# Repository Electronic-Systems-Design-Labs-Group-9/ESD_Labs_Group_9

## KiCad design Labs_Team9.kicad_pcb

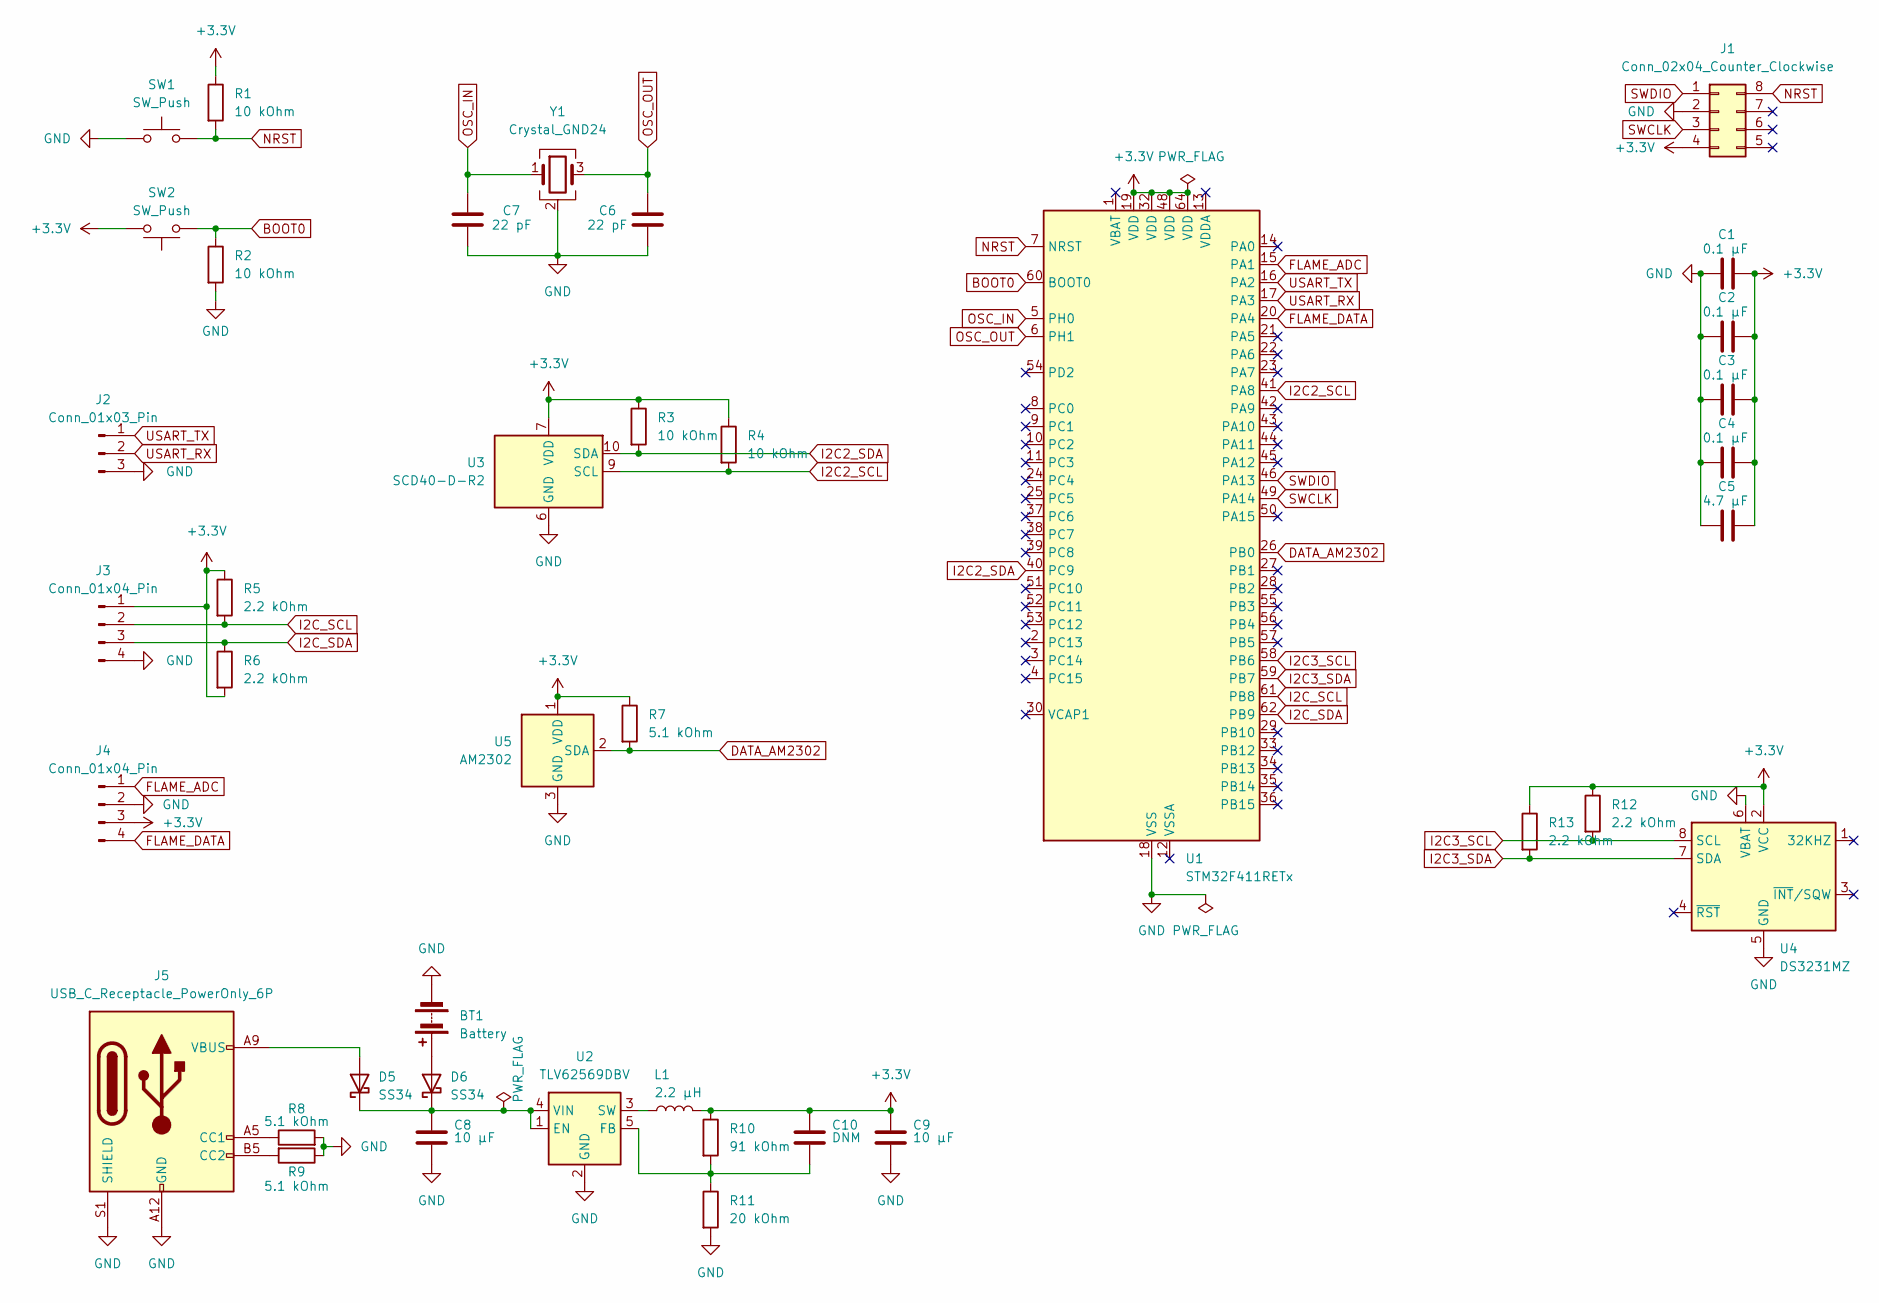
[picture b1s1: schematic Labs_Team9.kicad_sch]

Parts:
BT1: Battery; BatteryHolder_Keystone_2479_3xAAA
C1, C2, C3, C4: 0.1 μF; C_1206_3216Metric_Pad1.33x1.80mm_HandSolder
C5: 4.7 μF; C_1206_3216Metric_Pad1.33x1.80mm_HandSolder
C6, C7: 22 pF; C_1206_3216Metric_Pad1.33x1.80mm_HandSolder
C8, C9: 10 μF; C_1206_3216Metric_Pad1.33x1.80mm_HandSolder
C10: DNM; C_1206_3216Metric_Pad1.33x1.80mm_HandSolder
D5, D6: SS34; D_SMA_Handsoldering
J1: Conn_02x04_Counter_Clockwise; PinHeader_2x04_P2.54mm_Vertical
J2: Conn_01x03_Pin; PinHeader_1x03_P2.54mm_Vertical
J3, J4: Conn_01x04_Pin; PinHeader_1x04_P2.54mm_Vertical
J5: USB_C_Receptacle_PowerOnly_6P; USB_C_Receptacle_GCT_USB4135-GF-A_6P_TopMnt_Horizontal
L1: 2.2 μH; L_0805_2012Metric_Pad1.05x1.20mm_HandSolder
R1, R2, R3, R4: 10 kOhm; R_1206_3216Metric_Pad1.30x1.75mm_HandSolder
R5, R6, R12, R13: 2.2 kOhm; R_1206_3216Metric_Pad1.30x1.75mm_HandSolder
R7, R8, R9: 5.1 kOhm; R_1206_3216Metric_Pad1.30x1.75mm_HandSolder
R10: 91 kOhm; R_1206_3216Metric_Pad1.30x1.75mm_HandSolder
R11: 20 kOhm; R_1206_3216Metric_Pad1.30x1.75mm_HandSolder
SW1, SW2: SW_Push; SW_PUSH_6mm
U1: STM32F411RETx; LQFP-64_10x10mm_P0.5mm
U2: TLV62569DBV; SOT-23-5
U3: SCD40-D-R2; Sensirion_SCD4x-1EP_10.1x10.1mm_P1.25mm_EP4.8x4.8mm
U4: DS3231MZ; SOIC-8_3.9x4.9mm_P1.27mm
U5: AM2302; ASAIR_AM2302_P2.54mm_Lead2.75mm_TabDown
Y1: Crystal_GND24; Crystal_SMD_Abracon_ABM3C-4Pin_5.0x3.2mm

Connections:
+3.3V: C1.2, C2.2, C3.2, C4.2, C5.2, C9.1, C10.1, J1.4, J3.1, J4.3, L1.2, R1.1, R3.1, R4.1, R5.1, R6.2, R7.1, R10.1, R12.1, R13.1, SW2.2, U1.19 (VDD), U1.32 (VDD), U1.48 (VDD), U1.64 (VDD), U3.7 (VDD), U3.19 (VDD), U4.2 (VCC), U5.1 (VDD)
BOOT0: R2.1, SW2.1, U1.60 (BOOT0)
DATA_AM2302: R7.2, U1.26 (PB0), U5.2 (SDA)
FLAME_ADC: J4.1, U1.15 (PA1)
FLAME_DATA: J4.4, U1.20 (PA4)
GND: BT1.2 (-), C1.1, C2.1, C3.1, C4.1, C5.1, C6.1, C7.2, C8.2, C9.2, J1.2, J2.3, J3.4, J4.2, J5.A12 (GND), J5.B12 (GND), J5.S1 (SHIELD), R2.2, R8.2, R9.1, R11.2, SW1.1, U1.18 (VSS), U1.31 (VSS), U1.47 (VSS), U1.63 (VSS), U2.2 (GND), U3.6 (GND), U3.20 (GND), U3.21 (GND), U4.5 (GND), U4.6 (VBAT), U5.3 (GND), U5.4 (GND), Y1.2 (G), Y1.4 (G)
I2C2_SCL: R4.2, U1.41 (PA8), U3.9 (SCL)
I2C2_SDA: R3.2, U1.40 (PC9), U3.10 (SDA)
I2C3_SCL: R12.2, U1.58 (PB6), U4.8 (SCL)
I2C3_SDA: R13.2, U1.59 (PB7), U4.7 (SDA)
I2C_SCL: J3.2, R5.2, U1.61 (PB8)
I2C_SDA: J3.3, R6.1, U1.62 (PB9)
NRST: J1.8, R1.2, SW1.2, U1.7 (NRST)
unnamed: BT1.1 (+), D6.2 (A)
unnamed: D5.2 (A), J5.A9 (VBUS), J5.B9 (VBUS)
unnamed: C8.1, D5.1 (K), D6.1 (K), U2.1 (EN), U2.4 (VIN)
unnamed: J5.A5 (CC1), R8.1
unnamed: J5.B5 (CC2), R9.2
unnamed: C10.2, R10.2, R11.1, U2.5 (FB)
unnamed: L1.1, U2.3 (SW)
OSC_IN: C7.1, U1.5 (PH0), Y1.1
OSC_OUT: C6.2, U1.6 (PH1), Y1.3
SWCLK: J1.3, U1.49 (PA14)
SWDIO: J1.1, U1.46 (PA13)
USART_RX: J2.2, U1.17 (PA3)
USART_TX: J2.1, U1.16 (PA2)

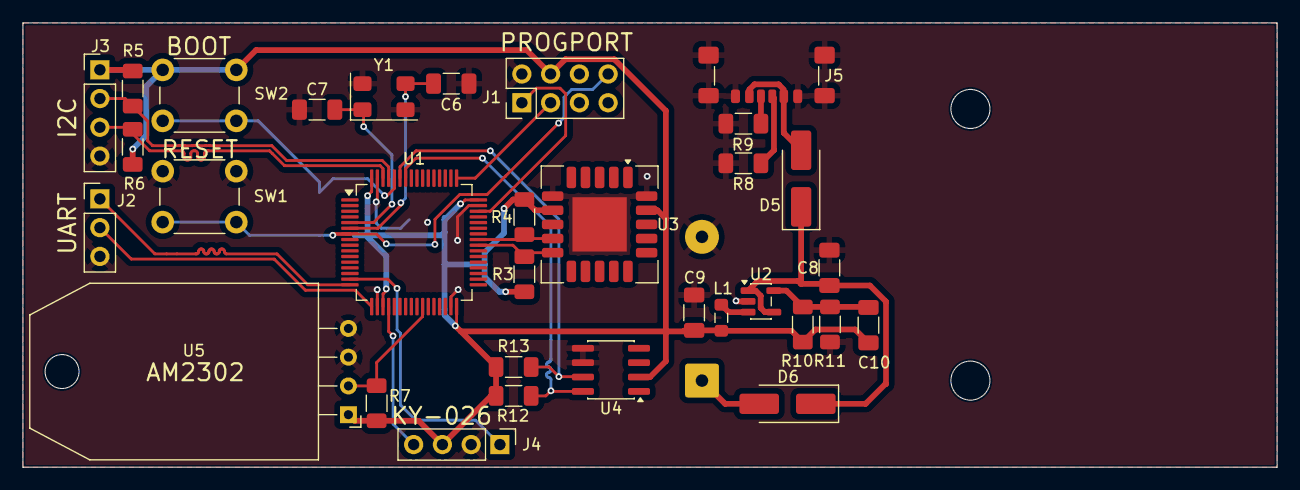
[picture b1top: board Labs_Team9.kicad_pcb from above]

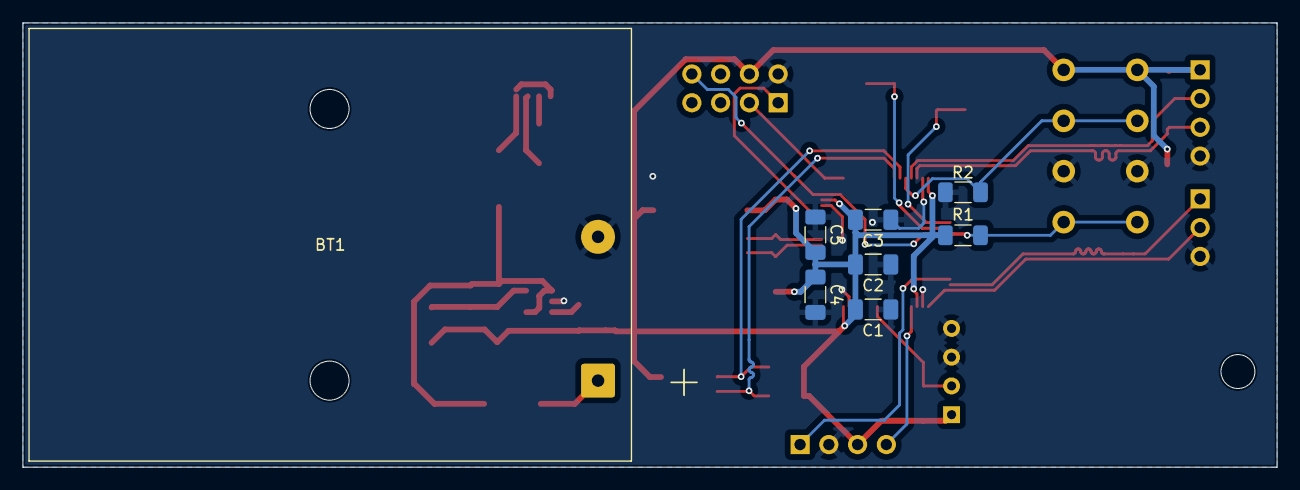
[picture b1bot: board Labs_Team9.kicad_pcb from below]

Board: 2 copper layers, 110.8 x 39.2 mm, 40 parts (8 on the bottom side), 26 nets.

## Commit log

2026-04-21 lab1: add schematic
2026-04-21 lab1: add tracing
2026-04-23 lab1: add simplified flowchart
2026-04-24 lab2: add schematic and part of the trace
2026-04-24 lab2: add full tracing
2026-04-25 lab2: add simplified flowchart
2026-04-25 lab3: add schematic
2026-04-26 lab3: add tracing
2026-04-26 lab3: add simplified flowchart
2026-04-28 lab4: add schematic and tracing
2026-04-28 lab4: add simplified flowchart
2026-05-16 lab5: add part of the schematic
2026-05-16 lab5: add full schematic
2026-05-16 lab5: add full tracing
2026-05-16 lab5: add simplified flowchart
2026-05-16 lab5: project cleanup
2026-05-17 lab5: fix
